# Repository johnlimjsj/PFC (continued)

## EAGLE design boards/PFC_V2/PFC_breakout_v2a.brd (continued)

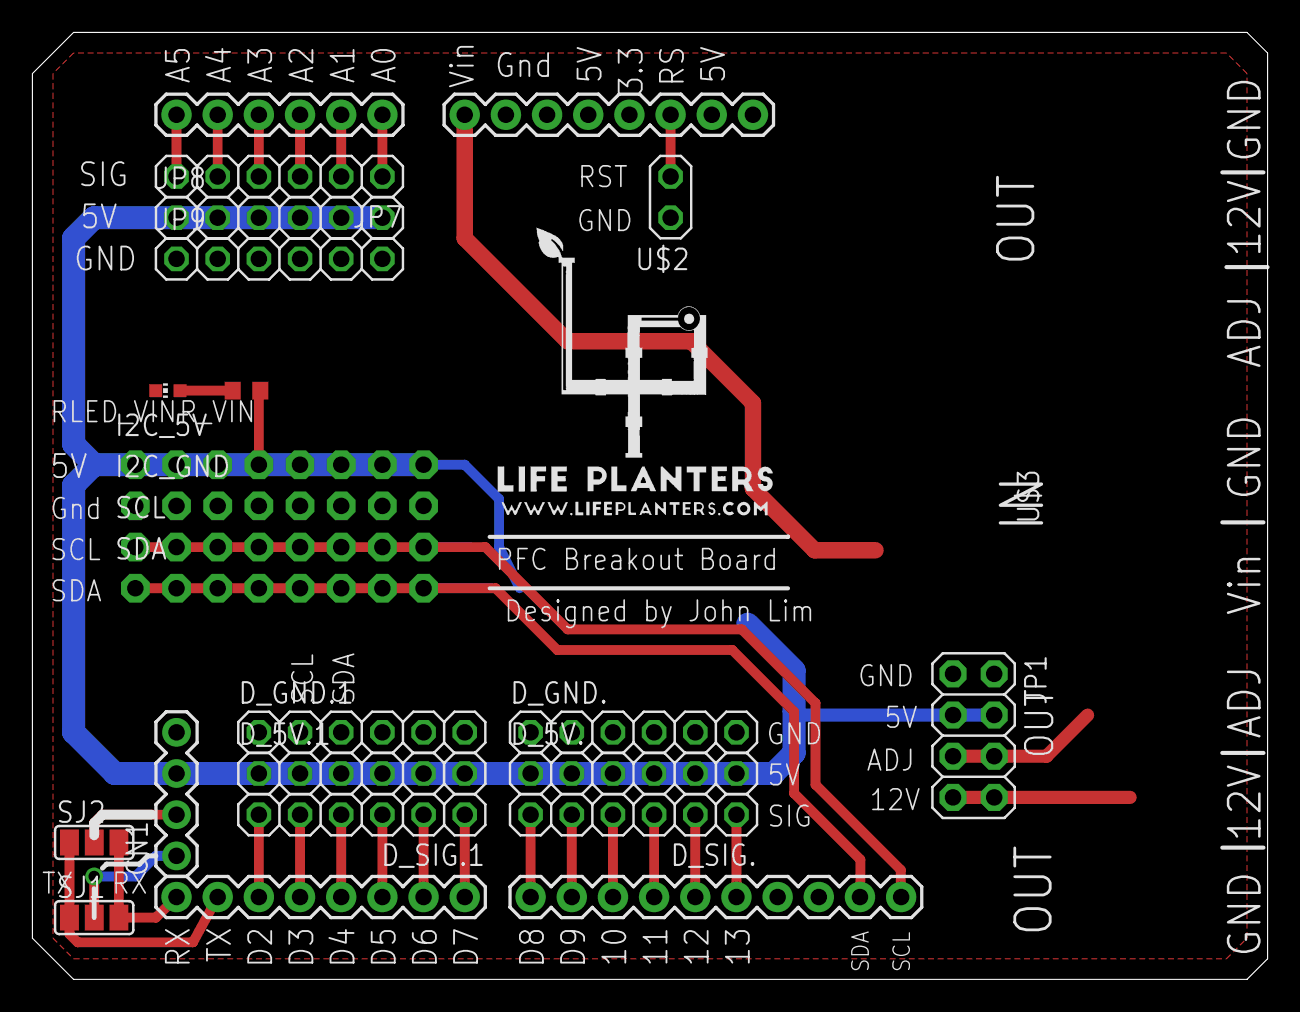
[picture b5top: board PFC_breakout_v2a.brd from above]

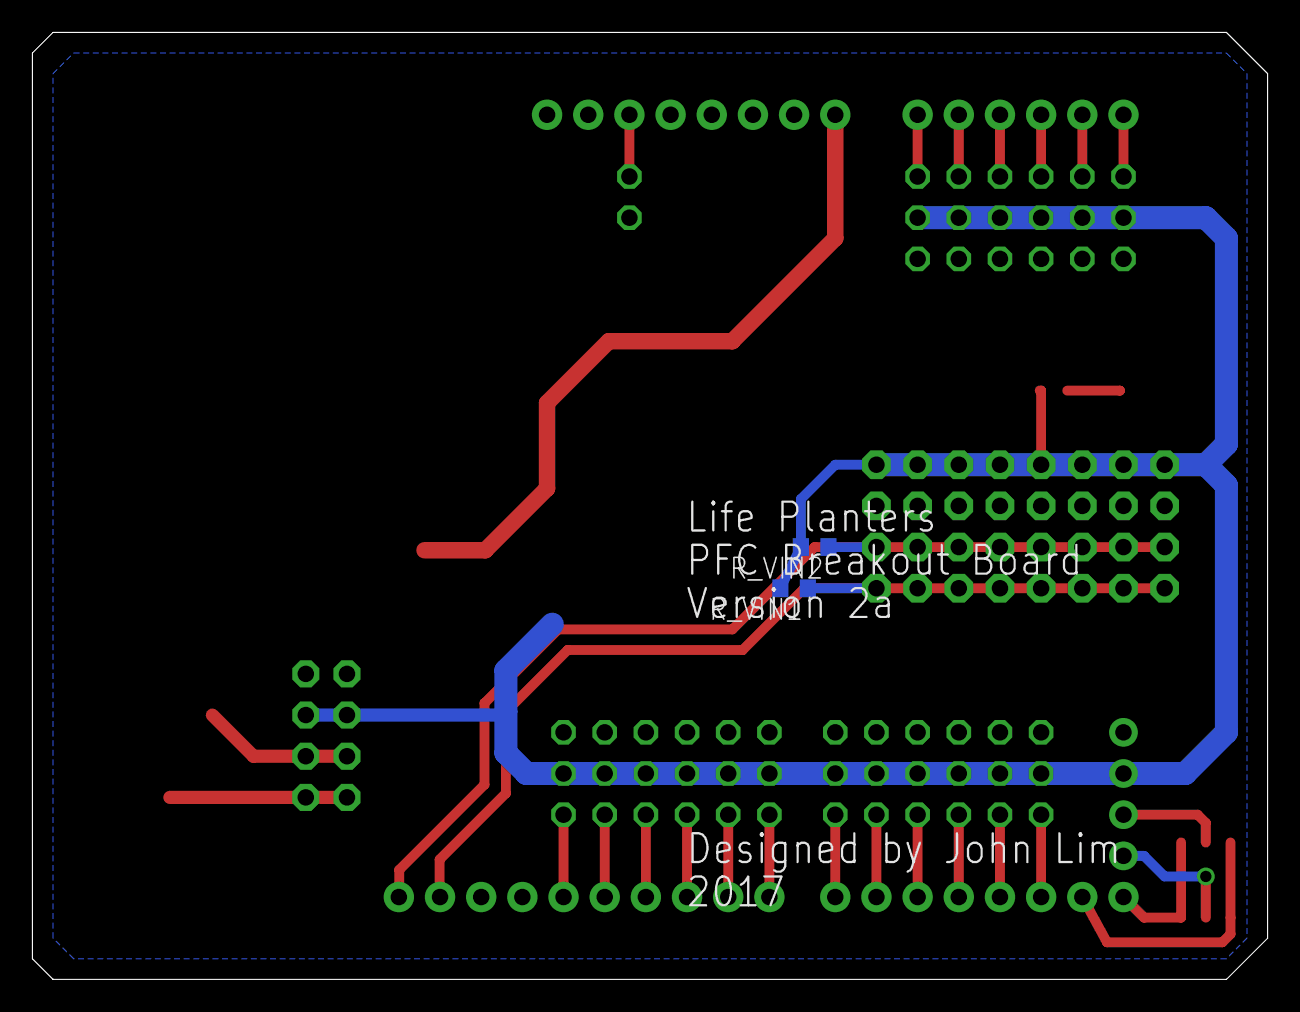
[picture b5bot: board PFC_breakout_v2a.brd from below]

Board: 2 copper layers, 76.2 x 58.4 mm, 24 parts (2 on the bottom side), 30 nets.

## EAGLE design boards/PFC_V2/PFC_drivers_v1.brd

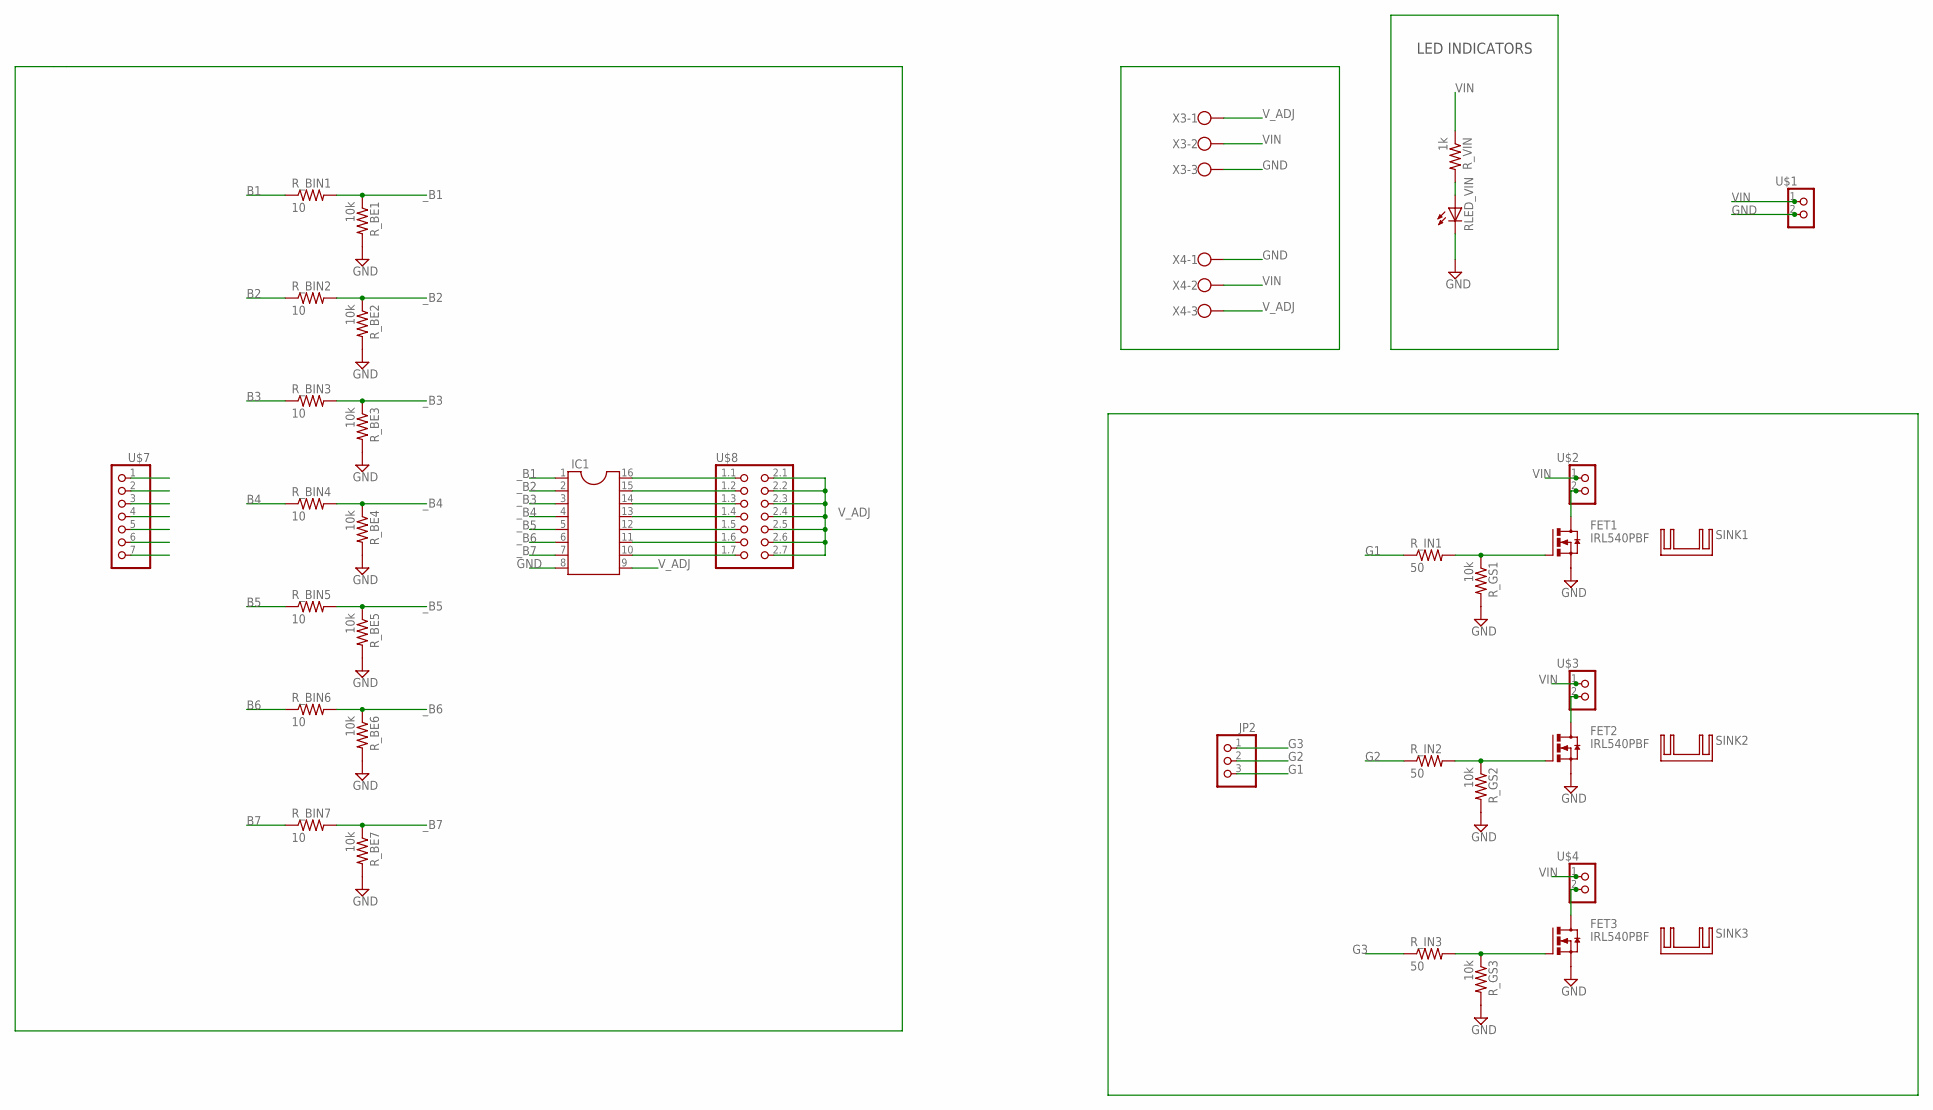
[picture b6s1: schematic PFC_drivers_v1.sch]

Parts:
FET1, FET2, FET3: IRL540PBF; TO220AV
IC1: DIL16S; SOCKET-16
JP2: PINHD-1X3; 1X03
RLED_VIN: LEDCHIP-LED0603; CHIP-LED0603
R_BE1, R_BE2, R_BE3, R_BE4, R_BE5, R_BE6, R_BE7: 10k; R0603
R_BIN1, R_BIN2, R_BIN3, R_BIN4, R_BIN5, R_BIN6, R_BIN7: 10; R0603
R_GS1, R_GS2, R_GS3: 10k; R0603
R_IN1, R_IN2, R_IN3: 50; R0603
R_VIN: 1k; R0603
SINK1, SINK2, SINK3: FW1S
U$1, U$2, U$3, U$4: PINHD-2X1; 2X01
U$7: PINHD-1X7; 1X07
U$8: PINHD-2X7; 2X07-BIG
X3, X4: W237-103

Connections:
B1: R_BIN1.1, U$7.1
B2: R_BIN2.1, U$7.2
B3: R_BIN3.1, U$7.3
B4: R_BIN4.1, U$7.4
B5: R_BIN5.1, U$7.5
B6: R_BIN6.1, U$7.6
B7: R_BIN7.1, U$7.7
G1: JP2.3, R_IN1.1
G2: JP2.2, R_IN2.1
G3: JP2.1, R_IN3.1
GND: FET1.E (S), FET2.E (S), FET3.E (S), IC1.8, RLED_VIN.C, R_BE1.2, R_BE2.2, R_BE3.2, R_BE4.2, R_BE5.2, R_BE6.2, R_BE7.2, R_GS1.2, R_GS2.2, R_GS3.2, U$1.2 (3), X3.3, X4.1
unnamed: RLED_VIN.A, R_VIN.2
unnamed: IC1.10, U$8.1.7
unnamed: IC1.11, U$8.1.6
unnamed: IC1.12, U$8.1.5
unnamed: IC1.13, U$8.1.4
unnamed: IC1.14, U$8.1.3
unnamed: IC1.15, U$8.1.2
unnamed: IC1.16, U$8.1.1
unnamed: FET1.C (D), U$2.2 (3)
unnamed: FET2.C (D), U$3.2 (3)
unnamed: FET3.C (D), U$4.2 (3)
VIN: R_VIN.1, U$1.1, U$2.1, U$3.1, U$4.1, X3.2, X4.2
V_ADJ: IC1.9, U$8.2.1, U$8.2.2, U$8.2.3, U$8.2.4, U$8.2.5, U$8.2.6, U$8.2.7, X3.1, X4.3
_B1: IC1.1, R_BE1.1, R_BIN1.2
_B2: IC1.2, R_BE2.1, R_BIN2.2
_B3: IC1.3, R_BE3.1, R_BIN3.2
_B4: IC1.4, R_BE4.1, R_BIN4.2
_B5: IC1.5, R_BE5.1, R_BIN5.2
_B6: IC1.6, R_BE6.1, R_BIN6.2
_B7: IC1.7, R_BE7.1, R_BIN7.2
_G1: FET1.B (G), R_GS1.1, R_IN1.2
_G2: FET2.B (G), R_GS2.1, R_IN2.2
_G3: FET3.B (G), R_GS3.1, R_IN3.2

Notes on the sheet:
LED INDICATORS

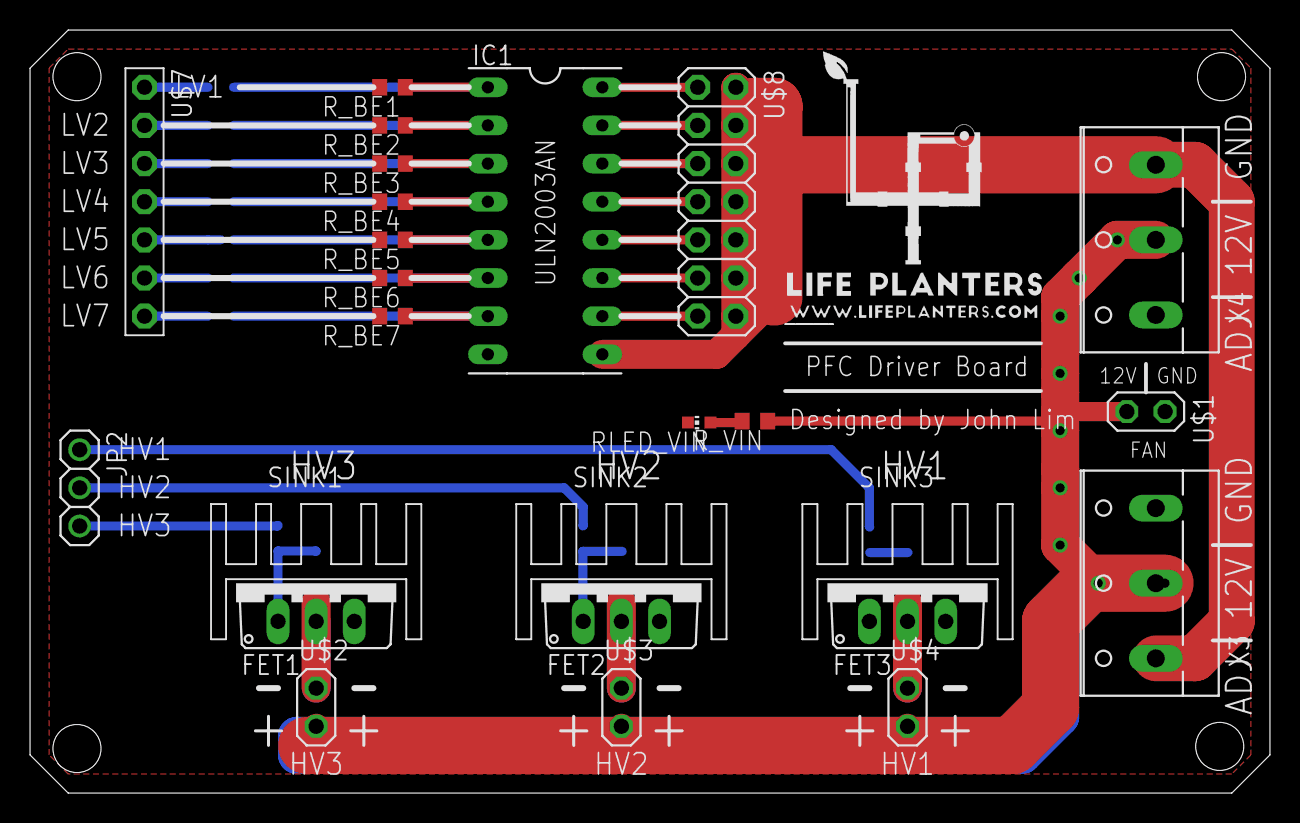
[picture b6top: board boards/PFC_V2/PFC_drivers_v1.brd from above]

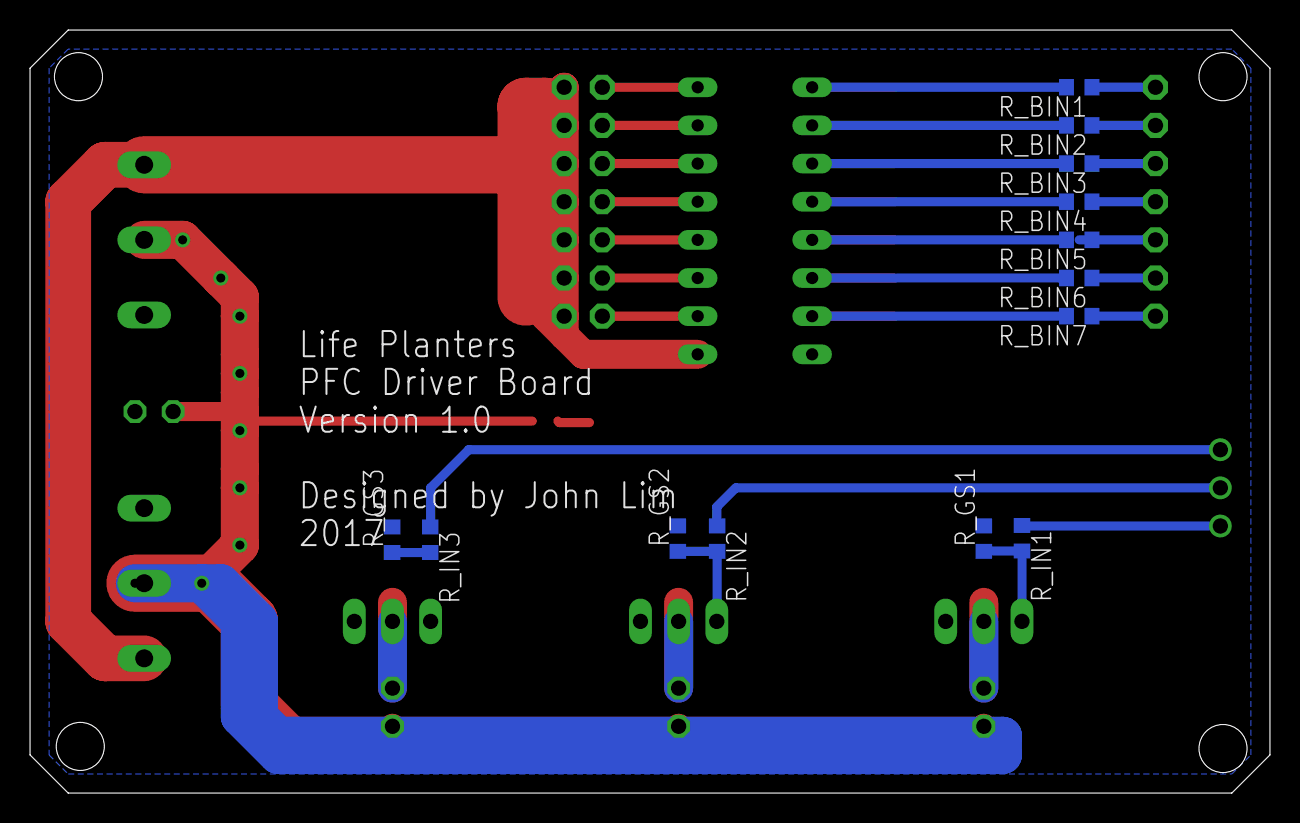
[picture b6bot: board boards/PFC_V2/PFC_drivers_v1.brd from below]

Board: 2 copper layers, 82.6 x 50.8 mm, 38 parts (13 on the bottom side), 34 nets.

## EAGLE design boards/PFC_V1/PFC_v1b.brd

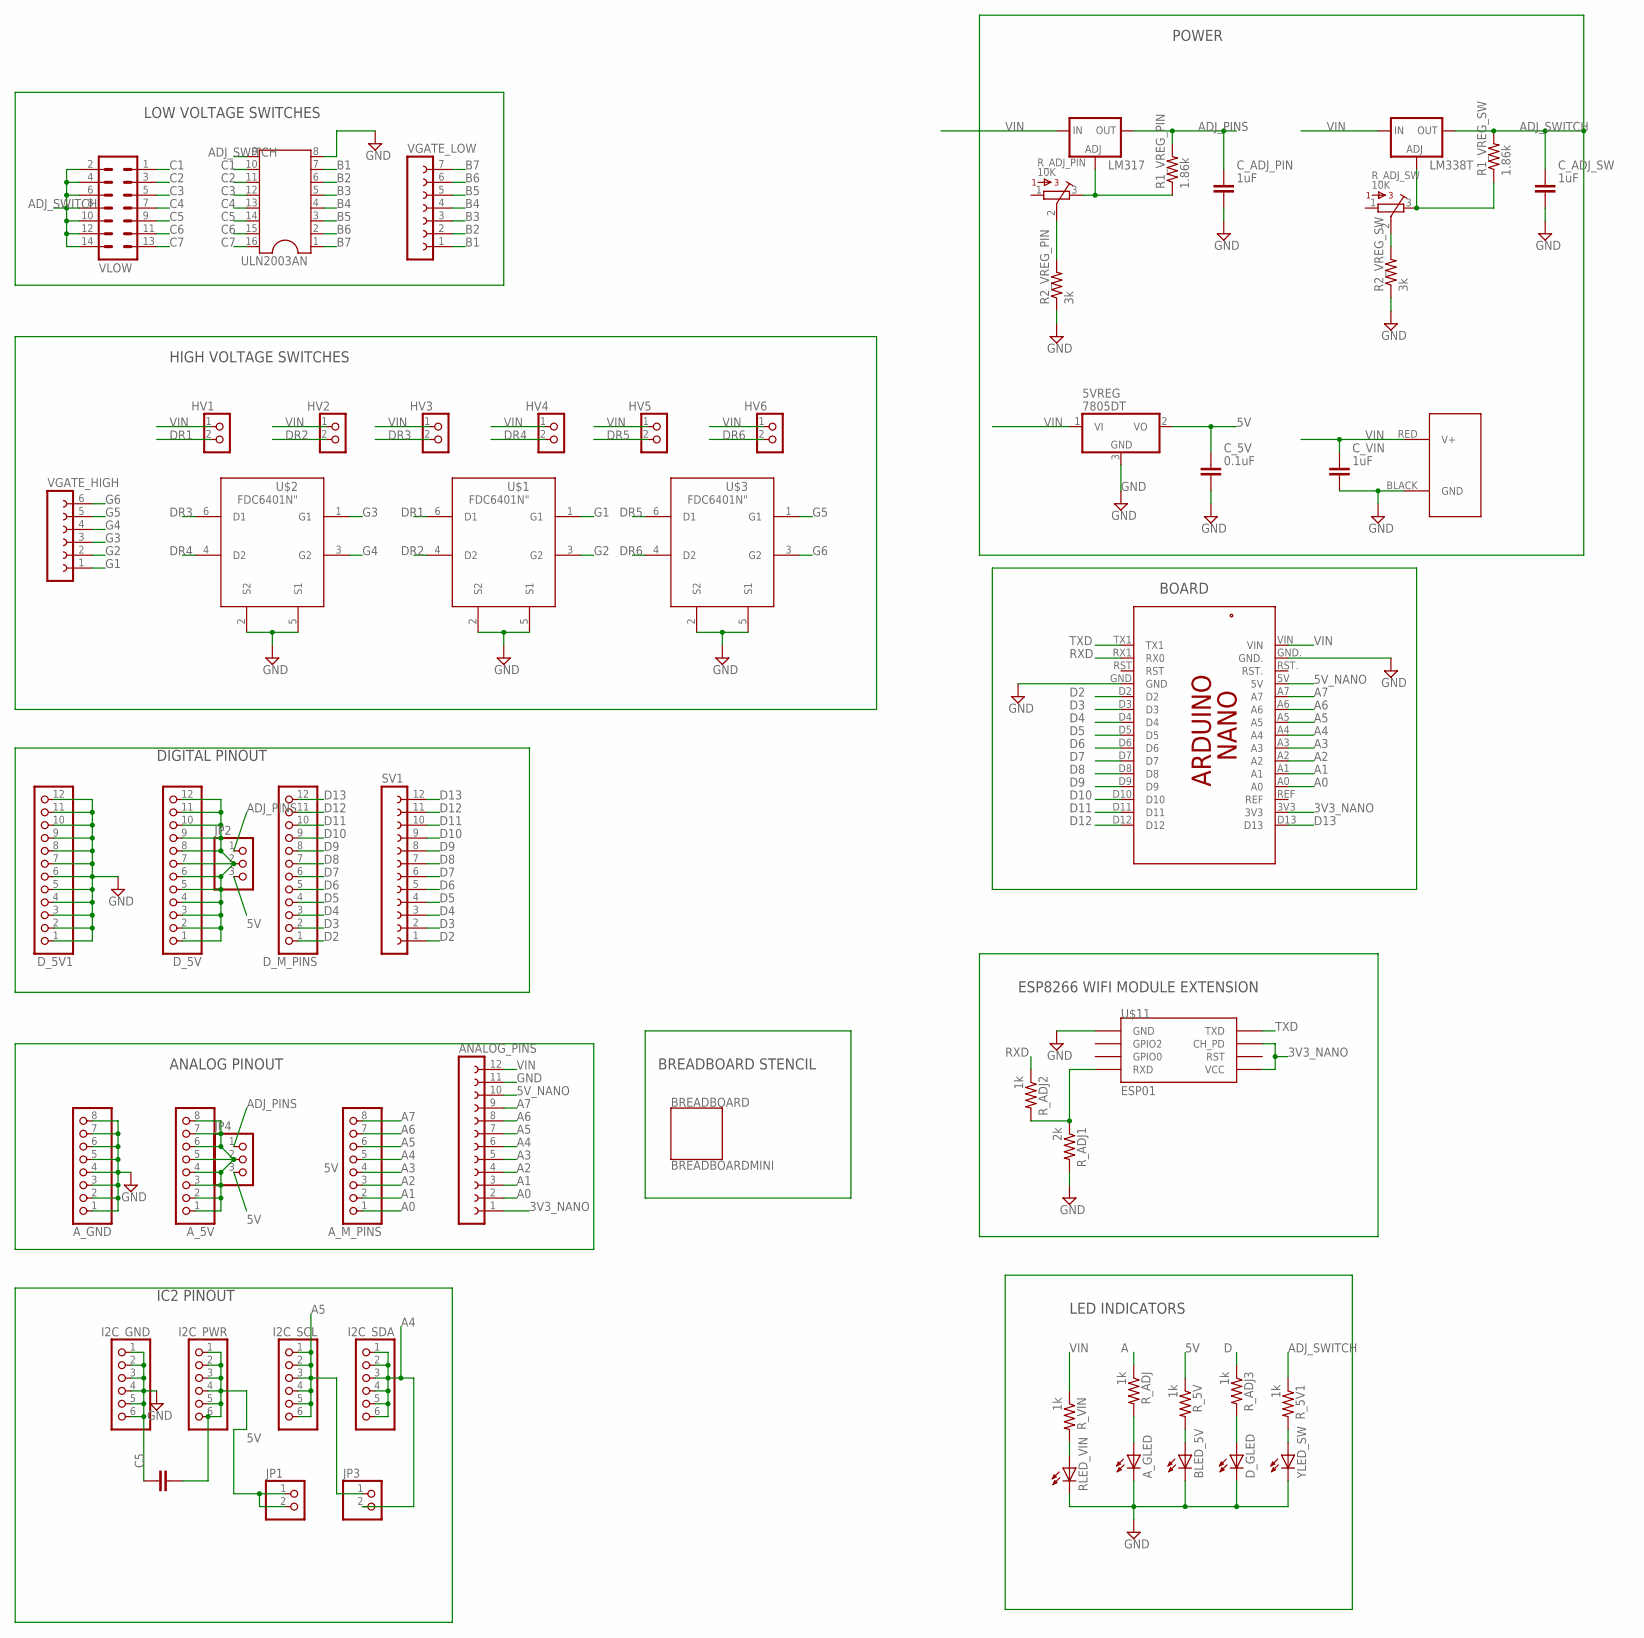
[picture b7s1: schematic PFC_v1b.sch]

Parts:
5VREG: 7805DT; TO252
ANALOG_PINS: FE12-1; FE12
A_5V: PINHD-1X8CLEANBIG; 1X08-CLEANBIG
A_GLED: LEDCHIP-LED0603; CHIP-LED0603
A_GND: PINHD-1X8CLEANBIG; 1X08-CLEANBIG
A_M_PINS: PINHD-1X8CLEANBIG; 1X08-CLEANBIG
BLED_5V: LEDCHIP-LED0603; CHIP-LED0603
BREADBOARD: BREADBOARDMINI; BREADBOARD-MINI
C5: CAPACITOR_NPOL-0603; C603
C_5V: 0.1uF; C603
C_ADJ_PIN: 1uF; C603
C_ADJ_SW: 1uF; C603
C_VIN: 1uF; C603
D_5V, D_5V1: PINHD-1X12-CB; 1X12-CB
D_GLED: LEDCHIP-LED0603; CHIP-LED0603
D_M_PINS: PINHD-1X12-CB; 1X12-CB
HV1, HV2, HV3, HV4, HV5, HV6: PINHD-2X1; 2X01
I2C_GND, I2C_PWR, I2C_SCL, I2C_SDA: PINHD-1X6CLEAN; 1X06-CLEAN
J1: POWERPOLE_POWER25A_HORIZONTAL_G2; POWERPOLE_PAIR_25A_HORIZ_G2
JP1, JP3: HEADER-1X2ROUND; 1X02_ROUND
JP2, JP4: PINHD-1X3CB; 1X03-CLEANBIG
LM317: LM317TL; 317TL
LM338T: LM138-TL; TO220L1
PCB1: ARDUINO_NANO_SHIELD
R1_VREG_PIN, R1_VREG_SW: 1.86k; R0603
R2_VREG_PIN, R2_VREG_SW: 3k; R0603
RLED_VIN: LEDCHIP-LED0603; CHIP-LED0603
R_5V, R_5V1: 1k; R0603
R_ADJ, R_ADJ2, R_ADJ3: 1k; R0603
R_ADJ1: 2k; R0603
R_ADJ_PIN: 10K; 3386P
R_ADJ_SW: 10K; 3386P
R_VIN: 1k; R0603
SV1: FE12-1; FE12
U$1, U$2, U$3: FDC6401N"; SSOT-6
U$11: ESP01
ULN2003AN: DIL16S; SOCKET-16
VGATE_HIGH: FE06-1; FE06
VGATE_LOW: FE07-1; FE07
VLOW: MA07-2
YLED_SW: LEDCHIP-LED0603; CHIP-LED0603

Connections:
3V3_NANO: ANALOG_PINS.1, PCB1.3V3, U$11.CH_PD, U$11.VCC
5V: 5VREG.2 (VO), C5.2, C_5V.1, I2C_PWR.1, I2C_PWR.2, I2C_PWR.3, I2C_PWR.4, I2C_PWR.5, I2C_PWR.6, JP1.1, JP1.2, JP2.3, JP4.3, R_5V.1
5V_NANO: ANALOG_PINS.10, PCB1.5V
$U: R_ADJ1.1, R_ADJ2.2, U$11.RX (RXD)
A: A_5V.1, A_5V.2, A_5V.3, A_5V.4, A_5V.5, A_5V.6, A_5V.7, A_5V.8, JP4.2, R_ADJ.1
A0: ANALOG_PINS.2, A_M_PINS.1, PCB1.A0
A1: ANALOG_PINS.3, A_M_PINS.2, PCB1.A1
A2: ANALOG_PINS.4, A_M_PINS.3, PCB1.A2
A3: ANALOG_PINS.5, A_M_PINS.4, PCB1.A3
A4: ANALOG_PINS.6, A_M_PINS.5, I2C_SDA.1, I2C_SDA.2, I2C_SDA.3, I2C_SDA.4, I2C_SDA.5, I2C_SDA.6, JP3.2, PCB1.A4
A5: ANALOG_PINS.7, A_M_PINS.6, I2C_SCL.1, I2C_SCL.2, I2C_SCL.3, I2C_SCL.4, I2C_SCL.5, I2C_SCL.6, JP3.1, PCB1.A5
A6: ANALOG_PINS.8, A_M_PINS.7, PCB1.A6
A7: ANALOG_PINS.9, A_M_PINS.8, PCB1.A7
ADJ_PINS: C_ADJ_PIN.1, JP2.1, JP4.1, LM317.2 (OUT), R1_VREG_PIN.2
ADJ_SWITCH: C_ADJ_SW.1, LM338T.2 (OUT), R1_VREG_SW.2, R_5V1.1, ULN2003AN.9, VLOW.2, VLOW.4, VLOW.6, VLOW.8, VLOW.10, VLOW.12, VLOW.14
B1: ULN2003AN.7, VGATE_LOW.1
B2: ULN2003AN.6, VGATE_LOW.2
B3: ULN2003AN.5, VGATE_LOW.3
B4: ULN2003AN.4, VGATE_LOW.4
B5: ULN2003AN.3, VGATE_LOW.5
B6: ULN2003AN.2, VGATE_LOW.6
B7: ULN2003AN.1, VGATE_LOW.7
C1: ULN2003AN.10, VLOW.1
C2: ULN2003AN.11, VLOW.3
C3: ULN2003AN.12, VLOW.5
C4: ULN2003AN.13, VLOW.7
C5: ULN2003AN.14, VLOW.9
C6: ULN2003AN.15, VLOW.11
C7: ULN2003AN.16, VLOW.13
D: D_5V.1, D_5V.2, D_5V.3, D_5V.4, D_5V.5, D_5V.6, D_5V.7, D_5V.8, D_5V.9, D_5V.10, D_5V.11, D_5V.12, JP2.2, R_ADJ3.1
D2: D_M_PINS.1, PCB1.D2, SV1.1
D3: D_M_PINS.2, PCB1.D3, SV1.2
D4: D_M_PINS.3, PCB1.D4, SV1.3
D5: D_M_PINS.4, PCB1.D5, SV1.4
D6: D_M_PINS.5, PCB1.D6, SV1.5
D7: D_M_PINS.6, PCB1.D7, SV1.6
D8: D_M_PINS.7, PCB1.D8, SV1.7
D9: D_M_PINS.8, PCB1.D9, SV1.8
D10: D_M_PINS.9, PCB1.D10, SV1.9
D11: D_M_PINS.10, PCB1.D11, SV1.10
D12: D_M_PINS.11, PCB1.D12, SV1.11
D13: D_M_PINS.12, PCB1.D13, SV1.12
DR1: HV1.2 (3), U$1.6 (D1)
DR2: HV2.2 (3), U$1.4 (D2)
DR3: HV3.2 (3), U$2.6 (D1)
DR4: HV4.2 (3), U$2.4 (D2)
DR5: HV5.2 (3), U$3.6 (D1)
DR6: HV6.2 (3), U$3.4 (D2)
G1: U$1.1 (G1), VGATE_HIGH.1
G2: U$1.3 (G2), VGATE_HIGH.2
G3: U$2.1 (G1), VGATE_HIGH.3
G4: U$2.3 (G2), VGATE_HIGH.4
G5: U$3.1 (G1), VGATE_HIGH.5
G6: U$3.3 (G2), VGATE_HIGH.6
GND: 5VREG.3 (GND), ANALOG_PINS.11, A_GLED.C, A_GND.1, A_GND.2, A_GND.3, A_GND.4, A_GND.5, A_GND.6, A_GND.7, A_GND.8, BLED_5V.C, C5.1, C_5V.2, C_ADJ_PIN.2, C_ADJ_SW.2, C_VIN.2, D_5V1.1, D_5V1.2, D_5V1.3, D_5V1.4, D_5V1.5, D_5V1.6, D_5V1.7, D_5V1.8, D_5V1.9, D_5V1.10, D_5V1.11, D_5V1.12, D_GLED.C, I2C_GND.1, I2C_GND.2, I2C_GND.3, I2C_GND.4, I2C_GND.5, I2C_GND.6, J1.BLACK (GND), PCB1.GND, PCB1.GND., R2_VREG_PIN.1, R2_VREG_SW.1, RLED_VIN.C, R_ADJ1.2, U$1.2 (S2), U$1.5 (S1), U$2.2 (S2), U$2.5 (S1), U$3.2 (S2), U$3.5 (S1), U$11.GND, ULN2003AN.8, YLED_SW.C
unnamed: RLED_VIN.A, R_VIN.2
unnamed: R2_VREG_SW.2, R_ADJ_SW.2
unnamed: A_GLED.A, R_ADJ.2
unnamed: BLED_5V.A, R_5V.2
unnamed: LM338T.1 (ADJ), R1_VREG_SW.1, R_ADJ_SW.3
unnamed: D_GLED.A, R_ADJ3.2
unnamed: R_5V1.2, YLED_SW.A
unnamed: LM317.1 (ADJ), R1_VREG_PIN.1, R_ADJ_PIN.3
unnamed: R2_VREG_PIN.2, R_ADJ_PIN.2
RXD: PCB1.RX1 (RX0), R_ADJ2.1
TXD: PCB1.TX1, U$11.TX (TXD)
VIN: 5VREG.1 (VI), ANALOG_PINS.12, C_VIN.1, HV1.1, HV2.1, HV3.1, HV4.1, HV5.1, HV6.1, J1.RED (V+), LM317.3 (IN), LM338T.3 (IN), PCB1.VIN, R_VIN.1

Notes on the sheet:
LOW VOLTAGE SWITCHES
HIGH VOLTAGE SWITCHES
DIGITAL PINOUT
ANALOG PINOUT
IC2 PINOUT
POWER
BOARD
ESP8266 WIFI MODULE EXTENSION
LED INDICATORS
BREADBOARD STENCIL

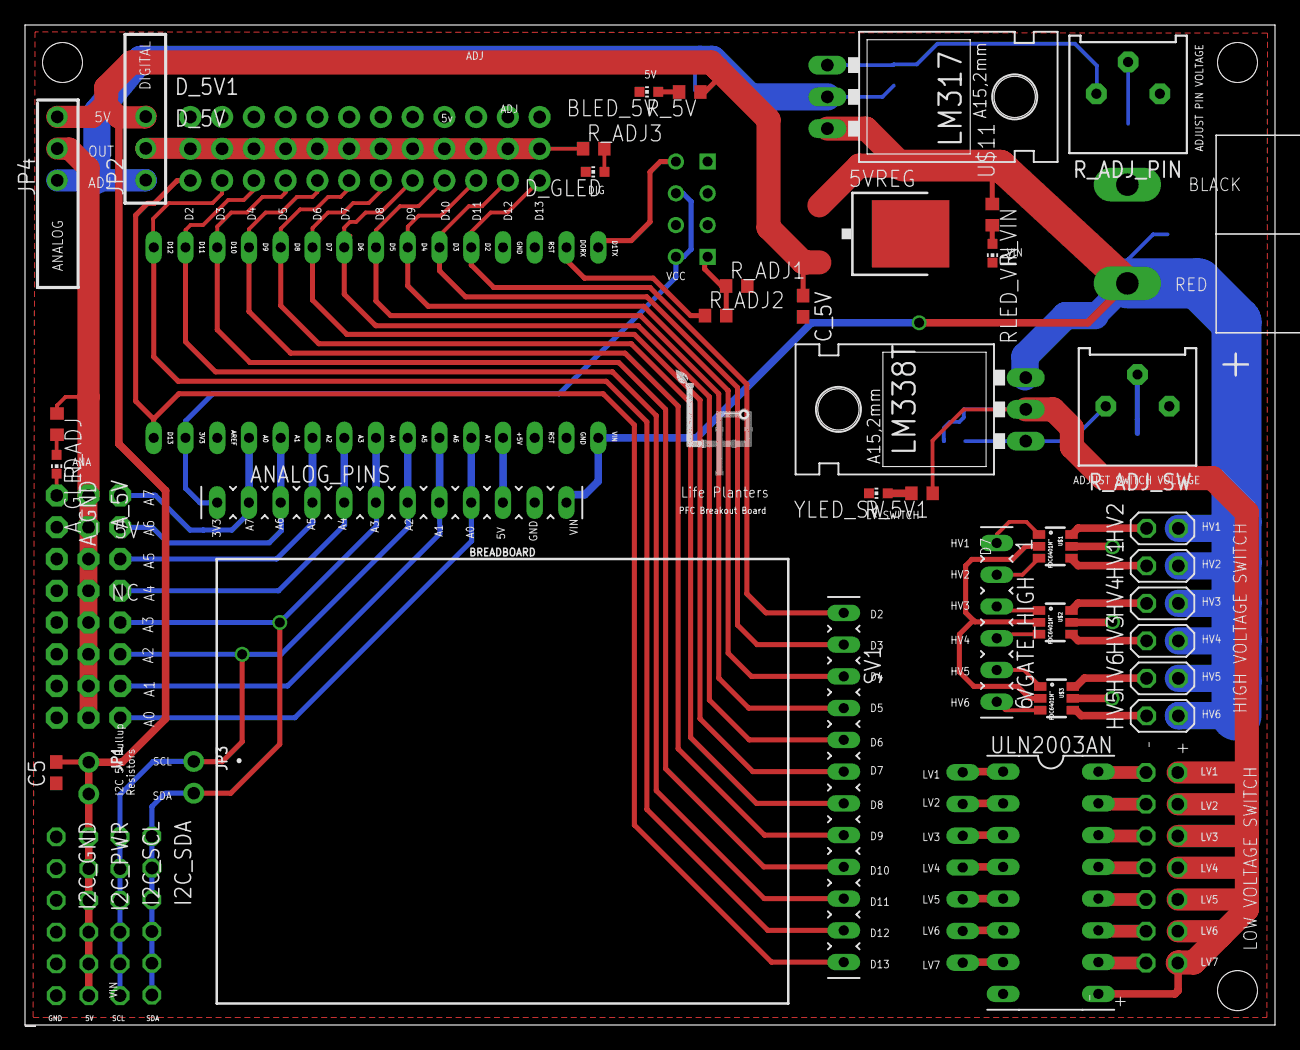
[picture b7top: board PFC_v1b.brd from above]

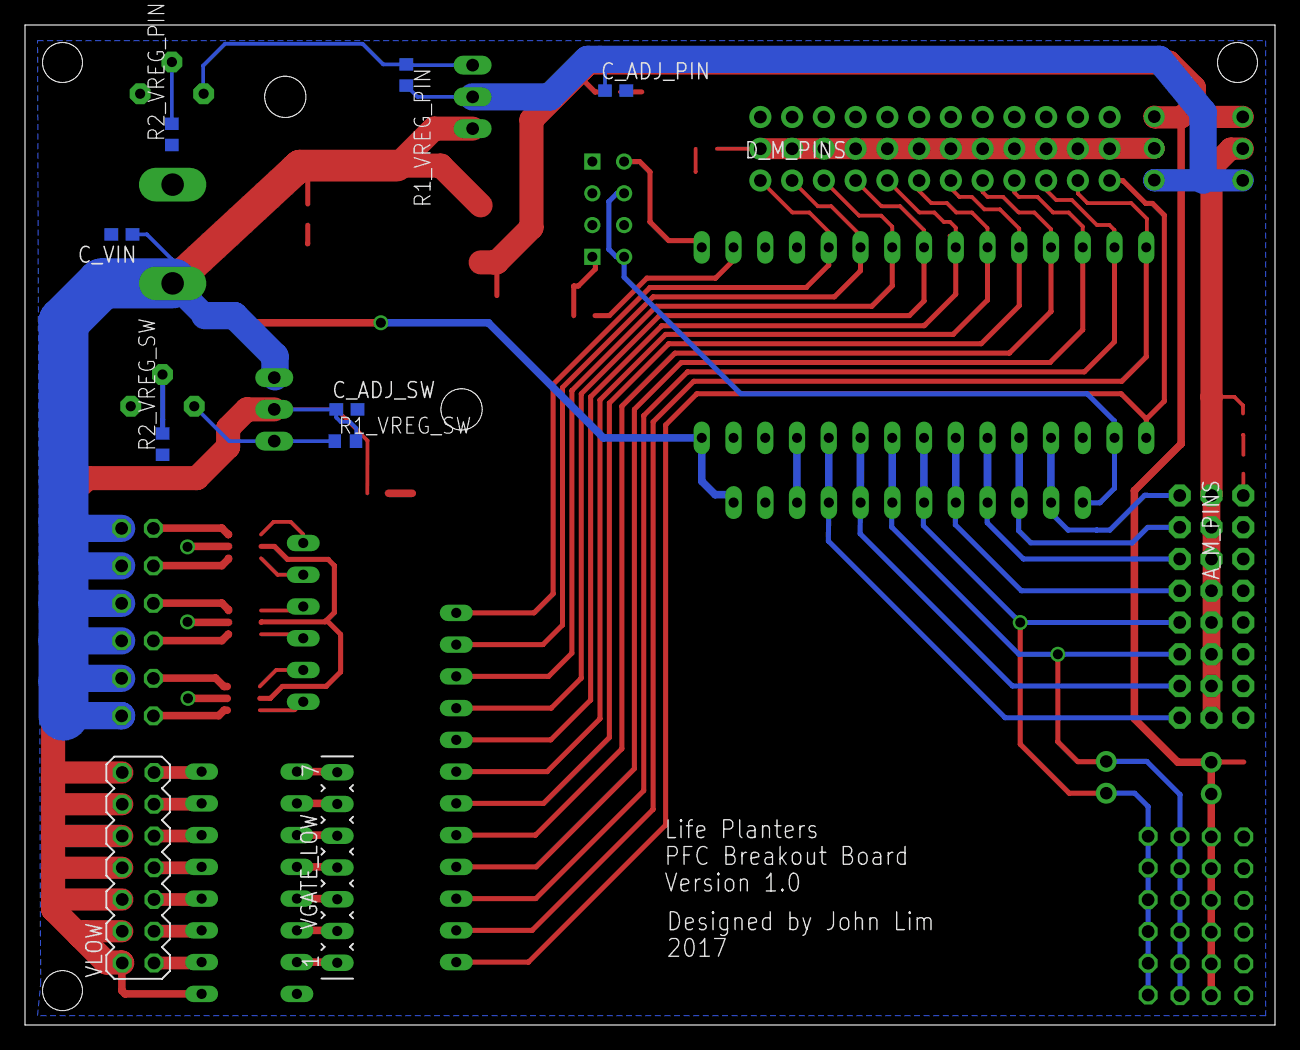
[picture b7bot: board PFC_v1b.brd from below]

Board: 2 copper layers, 100.0 x 80.0 mm, 59 parts (11 on the bottom side), 67 nets.

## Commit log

2017-03-16 first commit and initial source code
2017-06-26 version 1 testing
2017-07-08 changes made
2017-07-15 manual override
2017-07-16 fixed bug with manual actuation
2017-07-17 Commit before merging with origin
2017-07-21 manual override stuff and zul wifi
2017-07-23 minor changes to allow sensor send data without timeout on manual override
2017-08-08 added EEPROM and refactored out code to separate classes
2017-08-09 breaout board and driver board version 2
2017-08-09 fixed problem with the power fet driver
2017-09-05 completed ui of touch screen. No integration yet
2017-09-05 comments for pin mappings
2017-09-14 split code for sensors/actuators and for the ui/touch/wifi connectivity
2018-04-18 boards and src
2018-04-21 added i2chelper lib
2018-04-22 create ZIPLibrary folder
